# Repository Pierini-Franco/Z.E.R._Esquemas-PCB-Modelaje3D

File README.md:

# Z.E.R._Esquemas-PCB-Modelaje3D

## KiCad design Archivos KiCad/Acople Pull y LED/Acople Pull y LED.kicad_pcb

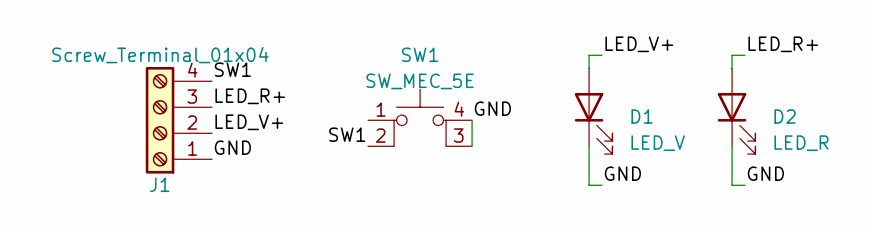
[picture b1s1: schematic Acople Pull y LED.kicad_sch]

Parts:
D1: LED_V; led_3mm_green
D2: LED_R; led_3mm_red
J1: Screw_Terminal_01x04; PinHeader_1x04_P2.54mm_Vertical
SW1: SW_MEC_5E; Pulsador_TH_4

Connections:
/GND: D1.1 (K), D2.1 (K), J1.1, SW1.3 (K), SW1.4 (A)
/LED_R+: D2.2 (A), J1.3
/LED_V+: D1.2 (A), J1.2
/SW1: J1.4, SW1.2

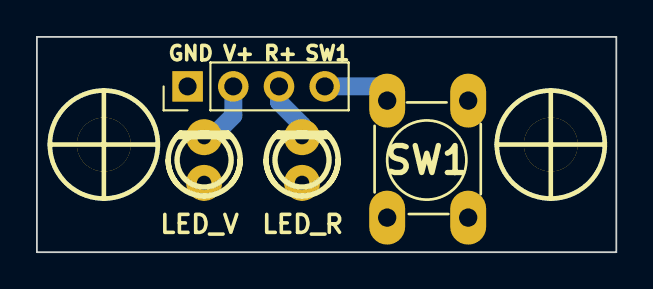
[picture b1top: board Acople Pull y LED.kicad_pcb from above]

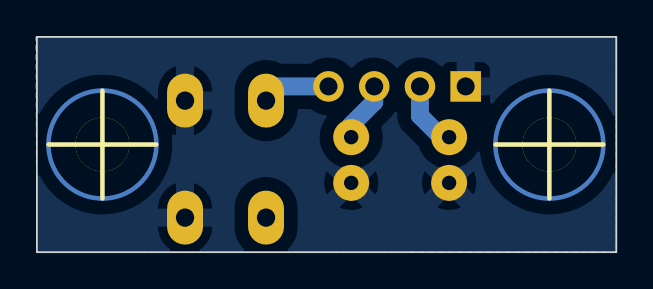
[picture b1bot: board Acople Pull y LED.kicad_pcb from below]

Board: 2 copper layers, 32.2 x 12.0 mm, 6 parts (2 on the bottom side), 4 nets.

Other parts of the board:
hole_3mm, hole_3mm#2: VAL**; hole_3mm

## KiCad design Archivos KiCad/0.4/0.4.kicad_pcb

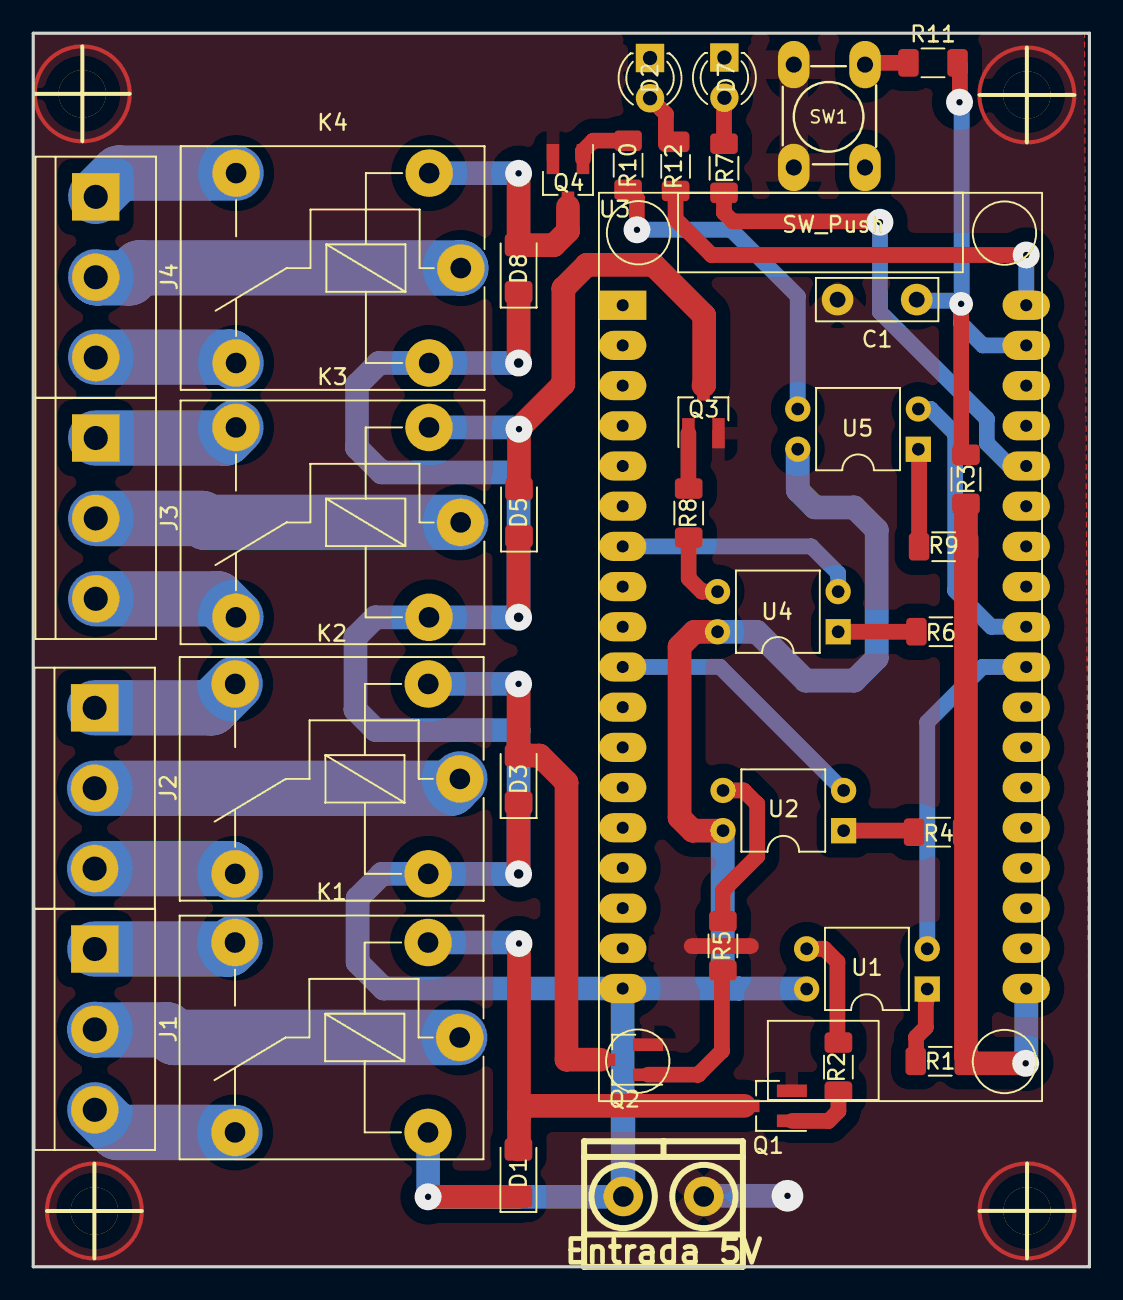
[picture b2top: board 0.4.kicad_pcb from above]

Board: 2 copper layers, 66.7 x 78.0 mm, 42 parts (0 on the bottom side), 41 nets.

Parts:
C1: C; C_Disc_D7.5mm_W2.5mm_P5.00mm
D1, D3, D5, D8: D_Shockley; D_1206_3216Metric_Pad1.42x1.75mm_HandSolder
D2, D7: LED; LED_D3.0mm
J1: Relay1; TerminalBlock_bornier-3_P5.08mm
J2: Relay2; TerminalBlock_bornier-3_P5.08mm
J3: Relay3; TerminalBlock_bornier-3_P5.08mm
J4: Relay4; TerminalBlock_bornier-3_P5.08mm
J6: Entrada 5V; BORNERA2_AZUL
K1, K2, K3, K4: G5V-1; Relay_SPDT_Finder_36.11
Q1, Q2, Q3, Q4: S8050; SOT-23_Handsoldering
R1, R2, R4, R5, R6, R8, R9, R10: 1k; R_1206_3216Metric_Pad1.30x1.75mm_HandSolder
R3, R11: 4,7k; R_1206_3216Metric_Pad1.30x1.75mm_HandSolder
R7, R12: 220; R_1206_3216Metric_Pad1.30x1.75mm_HandSolder
SW1: SW_Push; PUSH_SWITCH_THT
U1, U2, U4, U5: PC817; DIP-4_W7.62mm
U3: ESP32_DevKit_V1_DOIT; ESP32_Devkit_V1_36pin
hole_3mm, hole_3mm#2, hole_3mm#3, hole_3mm#4: VAL**; hole_3mm

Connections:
+3V3: R1.1, R3.1, R4.1, R6.1, R9.1, U3.19 (3V3)
+5V: D1.1 (K), D3.1 (K), D5.1 (K), D8.1 (K), J6.2, K1.2, K2.2, K3.2, K4.2, U1.4, U2.4, U3.18 (VIN), U4.4, U5.4
/BT_Config: C1.1, R3.2, R11.2, U3.35 (IO22)
/COM1: J1.2, K1.5
/COM2: J2.2, K2.5
/COM3: J3.2, K3.5
/COM4: J4.2, K4.5
/IN1: U1.2, U3.27 (RX2)
/IN2: U2.2, U3.10 (IO27)
/IN3: U3.7 (IO33), U4.2
/IN4: U3.28 (TX2), U5.2
/LED_ConfigBT: R12.1, U3.36 (IO23)
/LED_ConfigWIFI: R7.1, U3.32 (IO21)
/NC1: J1.3, K1.1
/NC2: J2.3, K2.1
/NC3: J3.3, K3.1
/NC4: J4.3, K4.1
/NO1: J1.1, K1.10
/NO2: J2.1, K2.10
/NO3: J3.1, K3.10
/NO4: J4.1, K4.10
GND: C1.2, D2.1 (K), D7.1 (K), J6.1, Q1.2 (E), Q2.2 (E), Q3.2 (E), Q4.2 (E), SW1.2, U3.17 (GND)
unnamed: D1.2 (A), K1.9, Q1.3 (C)
unnamed: D2.2 (A), R12.2
unnamed: D3.2 (A), K2.9, Q2.3 (C)
unnamed: D5.2 (A), K3.9, Q3.3 (C)
unnamed: D7.2 (A), R7.2
unnamed: D8.2 (A), K4.9, Q4.3 (C)
unnamed: Q1.1 (B), R2.2
unnamed: Q2.1 (B), R5.2
unnamed: Q3.1 (B), R8.2
unnamed: Q4.1 (B), R10.2
unnamed: R1.2, U1.1
unnamed: R2.1, U1.3
unnamed: R4.2, U2.1
unnamed: R5.1, U2.3
unnamed: R6.2, U4.1
unnamed: R8.1, U4.3
unnamed: R9.2, U5.1
unnamed: R10.1, U5.3
unnamed: R11.1, SW1.1
